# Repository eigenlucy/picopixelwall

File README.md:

# picopixelwall

Wooohooo a new package!

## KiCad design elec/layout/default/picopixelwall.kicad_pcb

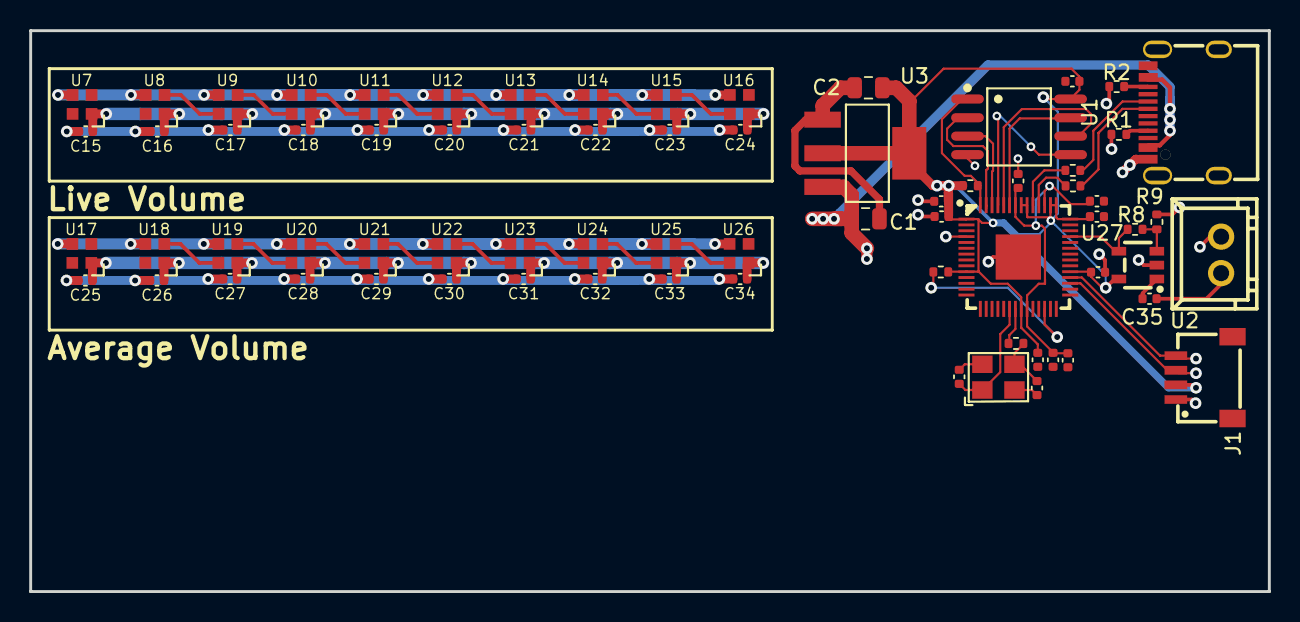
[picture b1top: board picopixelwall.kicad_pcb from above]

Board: 2 copper layers, 84.8 x 38.4 mm, 72 parts (0 on the bottom side), 46 nets.

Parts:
C1, C2: 25V 10uF X5R ±10% 0805 Multilayer Ceramic Capacit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; C0805
C3, C4: 50V 20pF C0G ±5% 0402 Multilayer Ceramic Capacito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; C0402
C5, C6, C7, C8, C9, C11, C12, C13, C15, C16, C17, C18, C19, C20, C21, C22, C23, C24, C25, C26, C27, C28, C29, C30, C31, C32, C33, C34: 16V 100nF X7R ±10% 0402 Multilayer Ceramic Capaci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; C0402
C10, C14: 25V 1uF X5R ±10% 0402 Multilayer Ceramic Capacito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; C0402
C35: 50V 10nF X7R ±10% 0402 Multilayer Ceramic Capacit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; C0402
J1: ?; CONN-SMD_4P-P1.00_SM04B-SRSS-TB-LF-SN
R1, R2: 62.5mW Thick Film Resistors 50V ±100ppm/℃ ±1% 5.1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; R0402
R3, R4, R8, R9: 62.5mW Thick Film Resistors 50V ±100ppm/℃ ±1% 10k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; R0402
R5: 62.5mW Thick Film Resistors 50V ±100ppm/℃ ±1% 1kΩ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; R0402
R6, R7: 62.5mW Thick Film Resistors 50V ±100ppm/℃ ±1% 27Ω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; R0402
U1: ?; USB-C-SMD_KH-TYPE-C-16P
U2: ?; CONN-TH_XH-2A
U3: ?; SOT-223-3_L6.5-W3.4-P2.30-LS7.0-BR
U4: ?; LQFN-56_L7.0-W7.0-P0.4-EP
U5: ?; OSC-SMD_4P-L3.2-W2.5-BL
U6: ?; SOIC-8_L5.3-W5.3-P1.27-LS8.0-BL
U7, U8, U9, U10, U11, U12, U13, U14, U15, U16, U17, U18, U19, U20, U21, U22, U23, U24, U25, U26: ?; LED-SMD_4P-L2.0-W2.0-BR
U27: ?; SOT-23-5_L3.0-W1.7-P0.95-LS2.8-BR

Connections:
audio_out: R8.1, U4.39, U27.4
cc1: R1.1, U1.A5
cc2: R2.1, U1.B5
dm: R7.1, U1.A7, U1.B7
dp: R6.2, U1.A6, U1.B6
gnd: C1.2, C2.2, C3.2, C4.2, C5.2, C6.2, C7.2, C8.2, C9.2, C10.2, C11.2, C12.2, C13.2, C14.2, C15.2, C16.2, C17.2, C18.2, C19.2, C20.2, C21.2, C22.2, C23.2, C24.2, C25.2, C26.2, C27.2, C28.2, C29.2, C30.2, C31.2, C32.2, C33.2, C34.2, J1.1, R1.2, R2.2, R9.2, U1.1, U1.2, U1.3, U1.4, U1.A1, U1.A12, U1.B1, U1.B12, U2.2, U3.1, U4.19, U4.57, U5.2, U5.4, U6.4, U7.3, U8.3, U9.3, U10.3, U11.3, U12.3, U13.3, U14.3, U15.3, U16.3, U17.3, U18.3, U19.3, U20.3, U21.3, U22.3, U23.3, U24.3, U25.3, U26.3, U27.2
gpio2: U4.4, U7.4
inverting: R8.2, R9.1, U27.3
io0: U4.53, U6.5
io1: U4.55, U6.2
io2: U4.54, U6.3
io3: U4.51, U6.7
ledrow1-dout: U16.2, U17.4
ledrow1.led1.ic-vcc: U7.2, U8.4
ledrow1.led2.ic-vcc: U8.2, U9.4
ledrow1.led3.ic-vcc: U9.2, U10.4
ledrow1.led4.ic-vcc: U10.2, U11.4
ledrow1.led5.ic-vcc: U11.2, U12.4
ledrow1.led6.ic-vcc: U12.2, U13.4
ledrow1.led7.ic-vcc: U13.2, U14.4
ledrow1.led8.ic-vcc: U14.2, U15.4
ledrow1.led9.ic-vcc: U15.2, U16.4
ledrow2.led1.ic-vcc: U17.2, U18.4
ledrow2.led2.ic-vcc: U18.2, U19.4
ledrow2.led3.ic-vcc: U19.2, U20.4
ledrow2.led4.ic-vcc: U20.2, U21.4
ledrow2.led5.ic-vcc: U21.2, U22.4
ledrow2.led6.ic-vcc: U22.2, U23.4
ledrow2.led7.ic-vcc: U23.2, U24.4
ledrow2.led8.ic-vcc: U24.2, U25.4
ledrow2.led9.ic-vcc: U25.2, U26.4
mic_connector-vcc: C35.1, U2.1
mic_in: C35.2, U27.1
micro-cs-1: R4.2, U4.56, U6.1
micro-sck-1: U4.52, U6.6
micro.micro-vcc: C11.1, C12.1, C13.1, C14.1, U4.23, U4.45, U4.50
out: C4.1, R5.2, U5.3
run: R3.2, U4.26
scl: J1.4, U4.32
sda: J1.3, U4.31
usb_dm: R7.2, U4.46
usb_dp: R6.1, U4.47
vcc-1: C1.1, C15.1, C16.1, C17.1, C18.1, C19.1, C20.1, C21.1, C22.1, C23.1, C24.1, C25.1, C26.1, C27.1, C28.1, C29.1, C30.1, C31.1, C32.1, C33.1, C34.1, U1.A4, U1.A9, U1.B4, U1.B9, U3.3, U7.1, U8.1, U9.1, U10.1, U11.1, U12.1, U13.1, U14.1, U15.1, U16.1, U17.1, U18.1, U19.1, U20.1, U21.1, U22.1, U23.1, U24.1, U25.1, U26.1
vcc-2: C2.1, C5.1, C6.1, C7.1, C8.1, C9.1, C10.1, J1.2, R3.1, R4.1, U3.2, U3.4, U4.1, U4.10, U4.22, U4.33, U4.42, U4.43, U4.44, U4.48, U4.49, U6.8, U27.5
xin: C3.1, U4.20, U5.1
xout: R5.1, U4.21

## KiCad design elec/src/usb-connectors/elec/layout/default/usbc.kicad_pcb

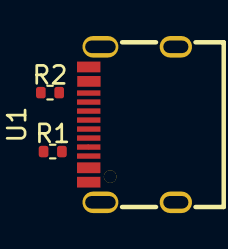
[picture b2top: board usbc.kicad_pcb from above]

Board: 2 copper layers, 3 parts (0 on the bottom side), 6 nets.

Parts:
R1, R2: Chip Resistor - Surface Mount 4.7KOhms ±5% 1/16W 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; R0402
U1: USB-C-SMD_KH-TYPE-C-16P

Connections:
cc1: R1.1, U1.A5
cc2: R2.1, U1.B5
dm: U1.A7, U1.B7
dp: U1.A6, U1.B6
gnd: R1.2, R2.2, U1.1, U1.2, U1.3, U1.4, U1.A1, U1.A12, U1.B1, U1.B12
vcc: U1.A4, U1.A9, U1.B4, U1.B9

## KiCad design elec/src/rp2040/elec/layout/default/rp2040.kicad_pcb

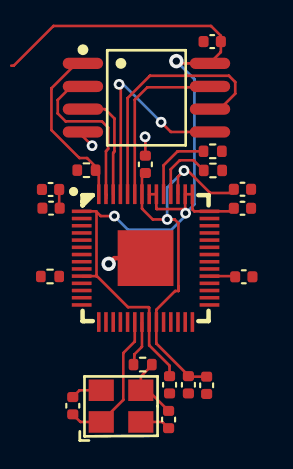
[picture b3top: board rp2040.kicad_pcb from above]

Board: 2 copper layers, 20 parts (0 on the bottom side), 15 nets.

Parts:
C1, C2: 50V 20pF C0G ±5% 0402 Multilayer Ceramic Capacito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; C0402
C3, C4, C5, C6, C7, C9, C10, C11: 16V 100nF X7R ±10% 0402 Multilayer Ceramic Capaci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; C0402
C8, C12: 25V 1uF X5R ±10% 0402 Multilayer Ceramic Capacito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; C0402
R1, R2: 62.5mW Thick Film Resistors ±100ppm/℃ ±1% 10kΩ 04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; R0402
R3: 62.5mW Thick Film Resistors ±100ppm/℃ ±1% 1kΩ 040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; R0402
R4, R5: 62.5mW Thick Film Resistors ±100ppm/℃ ±1% 27Ω 040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; R0402
U1: LQFN-56_L7.0-W7.0-P0.4-EP
U2: OSC-SMD_4P-L3.2-W2.5-BL
U3: SOIC-8_L5.3-W5.3-P1.27-LS8.0-BL

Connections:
cs-1: R2.2, U1.56, U3.1
gnd: C1.2, C2.2, C3.2, C4.2, C5.2, C6.2, C7.2, C8.2, C9.2, C10.2, C11.2, C12.2, U1.19, U1.57, U2.2, U2.4, U3.4
io0: U1.53, U3.5
io1: U1.55, U3.2
io2: U1.54, U3.3
io3: U1.51, U3.7
micro-vcc: C9.1, C10.1, C11.1, C12.1, U1.23, U1.45, U1.50
out: C2.1, R3.2, U2.3
run: R1.2, U1.26
sck-1: U1.52, U3.6
usb_dm: R5.2, U1.46
usb_dp: R4.1, U1.47
vcc: C3.1, C4.1, C5.1, C6.1, C7.1, C8.1, R1.1, R2.1, U1.1, U1.10, U1.22, U1.33, U1.42, U1.43, U1.44, U1.48, U1.49, U3.8
xin: C1.1, U1.20, U2.1
xout: R3.1, U1.21

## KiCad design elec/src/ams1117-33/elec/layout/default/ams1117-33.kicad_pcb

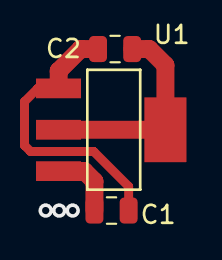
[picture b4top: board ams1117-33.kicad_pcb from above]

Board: 2 copper layers, 3 parts (0 on the bottom side), 3 nets.

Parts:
C1, C2: 25V 10uF X5R ±10% 0805 Multilayer Ceramic Capacit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; C0805
U1: SOT-223-3_L6.5-W3.4-P2.30-LS7.0-BR

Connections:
gnd: C1.2, C2.2, U1.1
vcc: C1.1, U1.3
vcc-1: C2.1, U1.2, U1.4

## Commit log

2024-10-23 working
2024-10-25 1024
2024-10-25 removed extra signals
2024-10-25 successful build
2024-10-25 great success
2024-10-28 working!!!
2024-10-29 meters
